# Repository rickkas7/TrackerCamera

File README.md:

# Tracker One Camera

This tutorial shows how to add a [4D Systems uCam-III](https://4dsystems.com.au/ucam-iii) to a Particle Tracker One to take pictures and upload them.

The caveat to this is that there is no built-in service for capturing or storing these image files in the cloud yet, but there's a simple demonstration server written in node.js that saves the files to disk. You can securely run this server even on a network using NAT (network address translation) without firewall changes. But the server is not intended to be used in production deployments. It's just an illustration of what is possible.

## The Process

While the camera may seem expensive, the reason for this specific camera is that it does JPEG compression in hardware. There is a serial interface to the MCU and a protocol for downloading the compressed image file. This eliminates the need to buffer the image in RAM to compress it. Since Particle devices generally have less than 80 Kbytes of free RAM, it's not possible to do compression of raw images on the MCU.

The camera connects to a small interface board which connects to the M8 connector on the Tracker One.

The image files are downloaded to the flash file system (LittleFS) on the Tracker for uploading when possible. This allows many images to be buffered even when there is currently no cellular signal.

When the Particle cloud is reachable, the image file is uploaded. The binary JPEG file is broken up into 423 byte chunks. Each of the chunks is Base64 encoded and published using the `NO_ACK` mode for speed and to minimize the data used by the ACKs. After the transmission is completed, the server sends either a done message, or a request to retransmit missing chunks. This repeats until all of the chunks have been received.

The image is verified using a SHA1 hash to make sure it was successfully received, and if so a message is sent from the server to tell the Tracker to delete the image. 

If you reboot the Tracker, it will upload any unsent files.

It takes about 25 seconds to upload a 320x240 pixel image. The image is only about 10 Kbytes, but the data usage is more than that because of the Base64 encoding needed to transport it in an event, and overhead.

It takes about 50 seconds to upload a 640x480 pixel image. 

## Connecting

The M8 (8mm) 8-pin connector on the Tracker One is standard, however it's not common. Some other connectors like M12 are more common, however, the 12mm connector would have required a taller enclosure to fit the larger connector. To simplify designs, Particle will provide a M8 female-to-wires cable, similar to this. This is for illustration only and the design may vary in the future.

The common use case will be to include a cable gland in your expansion enclosure, pass the wires through the gland, and terminate them on your custom expansion board.

You'd typically connect those wires to your custom expansion board using one of several methods:

- Terminate with pins in a PHR-8 to mate with a B8B-PH on your expansion board
- Terminate with screw terminals on your board
- Terminate by soldering the wires to your board

This example design is intended to be a prototype for illustration purposes only. It includes the same B8B-PH connector that is inside the Tracker One on the Tracker Carrier board. This connector is inexpensive and can be attached to the Tracker One Carrier Board or an eval adapter using an easy-to-build PHR-8 to PHR-8 cable:

If you are interested in prototyping designs intended to connect to the Tracker One M8 connector, but want to do it using the Tracker SoM Evaluation Board, you may be interested in [this project](https://github.com/rickkas7/M8-Eval-Adapter). It's only a set of design files, BoM, etc. and you'd need to fabricate the board and build it yourself; it's not available as a finished product. It also explains a bit more about how the M8 connector can be used.

## Hardware

There is a small board use to connect the Tracker One M8 connector to the camera. The board includes:

- Connector for connect to the M8 connector using screw terminals, a PHR-8 cable, or soldered wires.
- A XCL224 3.3V regulator
- Level shifters to convert the 5V camera UART signals to 3.3V needed by the Tracker One.
- A 5-pin camera connector

### Schematic

### Board Layout

### BoM

| Quantity | Part | Description | Example | Cost |
| :---: | :--- | :--- | :--- | ---: |
| 1 | C3 | Capacitor Ceramic 4.7uF 6.3V 0603 | [Murata GRM188R60J475KE19J](https://www.digikey.com/product-detail/en/murata-electronics-north-america/GRM188R60J475KE19J/490-6407-1-ND/3845604) | |
| 1 | C4 | Capacitor Ceramic 10uF 16V 0805 | [Murata GRM21BR61C106KE15L](https://www.digikey.com/product-detail/en/murata-electronics-north-america/GRM21BR61C106KE15L/490-3886-1-ND/965928) | |
| 1 | U2 | XCL224 3.3V regulator | [Torex XCL224A333D2-G](https://www.digikey.com/product-detail/en/torex-semiconductor-ltd/XCL224A333D2-G/893-1419-1-ND/8256121) |$ 2.43| 
| 2 | U1, U3 | IC TRNSLTR BIDIRECTIONAL SC70-6 | [TI SN74LVC1T45QDCKRQ1](https://www.digikey.com/product-detail/en/texas-instruments/SN74LVC1T45QDCKRQ1/296-39212-1-ND/5143211) | $0.60 |
|   | JP1 | Male Header Pins (8x0.1") | [Sullins PRPC040SAAN-RC](https://www.digikey.com/product-detail/en/PRPC040SAAN-RC/S1011EC-40-ND/2775214) | |

Choose one of:

| Quantity | Part | Description | Example | Cost | 
| :---: | :--- | :--- | :--- | ---: | 
| 1 | J1 | Conn SMD 8 position 2.00mm | [JST B8B-PH-SM4-TB(LF)(SN)](https://www.digikey.com/product-detail/en/jst-sales-america-inc/B8B-PH-SM4-TB-LF-SN/455-1740-1-ND/926837) | $1.00 |
|   | J2 | Male Header Pins (8x0.1") | [Sullins PRPC040SAAN-RC](https://www.digikey.com/product-detail/en/PRPC040SAAN-RC/S1011EC-40-ND/2775214) | |
| 1 | J2 | Screw Terminal Block 8x0.1" PTH | [On Shore OSTVN08A150](https://www.digikey.com/product-detail/en/on-shore-technology-inc/OSTVN08A150/ED10566-ND/1588868) | $2.36 | 

## Firmware

### Getting the Tracker Edge Firmware

The Tracker Edge firmware can be downloaded from Github:

[https://github.com/particle-iot/tracker-edge](https://github.com/particle-iot/tracker-edge)

After downloading the source, you will need to fetch the library dependencies. This can be done from a command prompt or terminal window with the git command line tools installed:

```
cd tracker-edge
git submodule init
git submodule update --recursive
```

Be sure to target 1.5.4-rc.1 or later for your build. Device OS 1.5.3 or later is required, only version 1.5.4-rc.1 and later are available in the full set of tools including Workbench, CLI, and Web IDE.

### Add the libraries

From the command palette in Workbench, **Particle: Install Library** then enter **CameraHelperRK**. 

If you prefer to edit project.properties directly, add these:

```
dependencies.CameraHelperRK=0.0.1
```

This library includes two other libraries, **uCamIII** to handle interacting with the camera and **Base64RK** to do the Base64 encoding.

### The full source

The firmware is pretty self-explanatory. There is a copy in source/main.cpp as well.

```cpp
#include "Particle.h"

#include "tracker_config.h"
#include "tracker.h"

#include "CameraHelperRK.h"

SYSTEM_THREAD(ENABLED);
SYSTEM_MODE(SEMI_AUTOMATIC);

PRODUCT_ID(TRACKER_PRODUCT_ID);
PRODUCT_VERSION(TRACKER_PRODUCT_VERSION);

SerialLogHandler logHandler(115200, LOG_LEVEL_INFO, {
    { "app.gps.nmea", LOG_LEVEL_INFO },
    { "app.gps.ubx",  LOG_LEVEL_INFO },
    { "ncp.at", LOG_LEVEL_INFO },
    { "net.ppp.client", LOG_LEVEL_INFO },
    { "app.cam", LOG_LEVEL_TRACE },
});

int takePictureHandler(String cmd);

CameraHelperTracker cameraHelper(Serial1, 115200);

void setup()
{
    Tracker::instance().init();

    Particle.function("takePicture", takePictureHandler);

    // Enable cloud configuration of settings    
    // cameraHelper.setupCloudConfig();

    // Start the camera interface
    // The CameraHelperTracker turns on the CAN_PWR to power the camera.
    cameraHelper.setup();

    Particle.connect();
}

void loop()
{
    Tracker::instance().loop();

    cameraHelper.loop();
}

int takePictureHandler(String cmd) 
{
    // Take a picture
    cameraHelper.takePicture();

    // Send the current location
    TrackerLocation::instance().triggerLocPub();
    return 0;
}

```

It registers a function so you can easy trigger taking a picture from the console.

```cpp
Particle.function("takePicture", takePictureHandler);
```

Of course you can easily do it from code as well:

```cpp
// Take a picture
cameraHelper.takePicture();
```

## Server

The server code is in the server directory. 

- Install the node dependencies:

```bash
npm install
```

- Get an [access token](https://docs.particle.io/reference/developer-tools/cli/#particle-token-create)

- Set it as an environment variable:

```bash
export AUTH_TOKEN=xxxxxxx
```

- Run the server. Be sure to specify the productId of your Tracker product!

```bash
node app.js --productId 1234
```

The server creates a directory `data`. Within that directory will be a directory each device ID that is publishing to the product.

When a picture is uploaded, the JPEG file is reconstituted and verified, and if the SHA1 hash matches, it's saved in the device directory with a timestamp as a filename. The most recent `loc` event for the same device is also saved as a .json file so you can get the matching location information.

### Cloud Configuration

If you uncomment the `setupCloudConfig()` call in main.cpp, you can configure the image parameters from the cloud!

```cpp
// Enable cloud configuration of settings    
// cameraHelper.setupCloudConfig();
```

The cloud configuration cannot be set from the console, but you can set it from the CLI using curl. 

```bash
curl -X PUT https://api.particle.io/v1/products/:productId/config/:deviceId?access_token=:accessToken -H "Content-Type: application/json" -d "{\"ucam\":{\"resolution\":5,\"contrast\":2,\"brightness\":2,\"exposure\":2}}"
```

Be sure to update:

`:productId` with your product ID
`:deviceId` with your Device ID that is set as a development device. If you want to change the contrast across your whole product leave off the slash and device ID.
`:accessToken` with a product access token. An easy way to get a temporary 

One easy way to get a temporary access token is to:

- Open the [console](https://console.particle.io).
- Open your Tracker product.
- Click on **Devices**.
- Open your device.
- In the **Events** tab, click on **View events from a terminal** (it's a button).
- Copy and paste the access token from the end of the command that is displayed.
- This token is invalidated when your close the console.

The parameters are:

- resolution:

  One of:
  - 1 80x60
  - 2 160x120
  - 3 160x128
  - 5 320x240 (default)
  - 7 640x480
  - 8 128x96
  - 9 128x128

- contrast:

  One of: 
  - 0 minimum
  - 1 low
  - 2 default
  - 3 high
  - 4 max

- brightness:

  One of: 
  - 0 minimum
  - 1 low
  - 2 default
  - 3 high
  - 4 max

- exposure:

  One of:
  - 0 exposure -2
  - 1 exposure -1
  - 2 exposure 0 (default)
  - 3 exposure +1
  - 4 exposure +2

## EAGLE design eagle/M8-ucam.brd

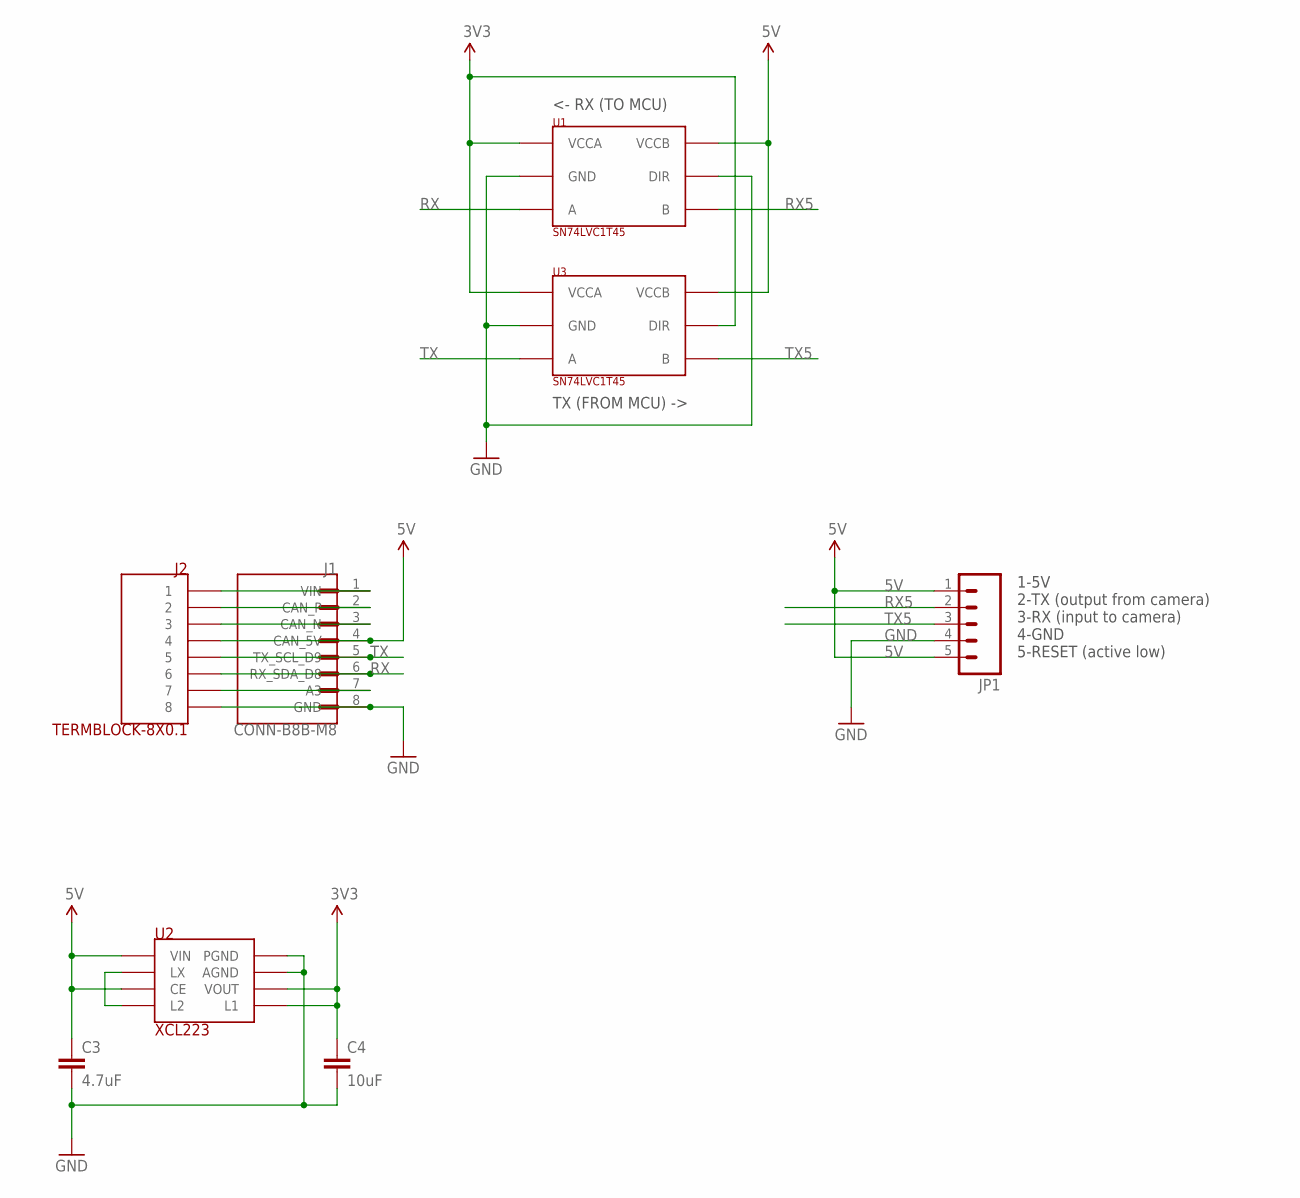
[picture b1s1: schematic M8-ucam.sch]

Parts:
C3: 4.7uF; 0603-CAP
C4: 10uF; 0603-CAP
J1: CONN-B8B-M8; JST_B8B-PH-SM4-TB(LF)(SN)
J2: TERMBLOCK-8X0.1
JP1: M05PTH; 1X05
U1, U3: SN74LVC1T45; SC70-TI
U2: XCL223; REG-XCL223-LESS-CREAM

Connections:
3V3: C4.1, U1.1 (VCCA), U2.3 (VOUT), U2.7 (L1), U3.1 (VCCA), U3.5 (DIR)
5V: C3.1, J1.4 (CAN_5V), J2.P$4 (4), JP1.1, JP1.5, U1.6 (VCCB), U2.4 (CE), U2.6 (VIN), U3.6 (VCCB)
A3: J1.7 (A3), J2.P$7 (7)
CAN_N: J1.3 (CAN_N), J2.P$3 (3)
CAN_P: J1.2 (CAN_P), J2.P$2 (2)
GND: C3.2, C4.2, J1.8 (GND), J2.P$8 (8), JP1.4, U1.2 (GND), U1.5 (DIR), U2.1 (PGND), U2.2 (AGND), U3.2 (GND)
LX: U2.5 (LX), U2.8 (L2)
RX: J1.6 (RX_SDA_D8), J2.P$6 (6), U1.3 (A)
RX5: JP1.2, U1.4 (B)
TX: J1.5 (TX_SCL_D9), J2.P$5 (5), U3.3 (A)
TX5: JP1.3, U3.4 (B)
VIN: J1.1 (VIN), J2.P$1 (1)

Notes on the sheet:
1-5V 2-TX (output from camera) 3-RX (input to camera) 4-GND 5-RESET (active low)
<- RX (TO MCU)
TX (FROM MCU) ->

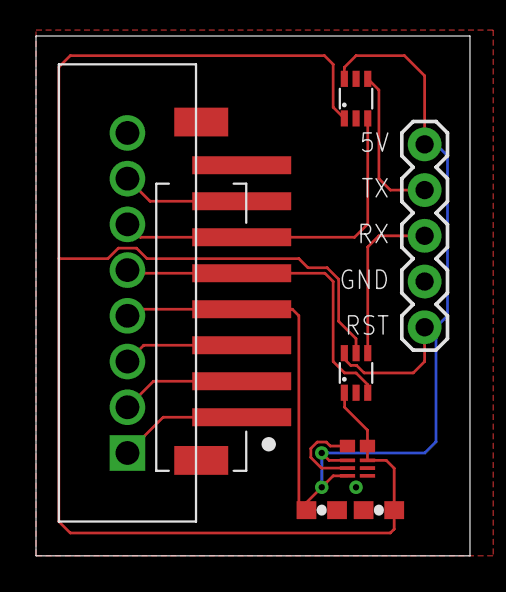
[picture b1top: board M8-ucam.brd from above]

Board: 2 copper layers, 24.1 x 28.9 mm, 8 parts (0 on the bottom side), 12 nets.

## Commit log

2020-07-26 Initial version
2020-07-26 Add Tracker Edge download instructions
2021-04-01 Bump y18n from 4.0.0 to 4.0.1 in /server
    Bumps [y18n](https://github.com/yargs/y18n) from 4.0.0 to 4.0.1.
    - [Release notes](https://github.com/yargs/y18n/releases)
    - [Changelog](https://github.com/yargs/y18n/blob/master/CHANGELOG.md)
    - [Commits](https://github.com/yargs/y18n/commits)
2022-12-06 Bump qs from 6.9.4 to 6.11.0 in /server
    Bumps [qs](https://github.com/ljharb/qs) from 6.9.4 to 6.11.0.
    - [Release notes](https://github.com/ljharb/qs/releases)
    - [Changelog](https://github.com/ljharb/qs/blob/main/CHANGELOG.md)
    - [Commits](https://github.com/ljharb/qs/compare/v6.9.4...v6.11.0)
    ---
    updated-dependencies:
2023-01-24 Bump cookiejar from 2.1.2 to 2.1.4 in /server
    Bumps [cookiejar](https://github.com/bmeck/node-cookiejar) from 2.1.2 to 2.1.4.
    - [Release notes](https://github.com/bmeck/node-cookiejar/releases)
    - [Commits](https://github.com/bmeck/node-cookiejar/commits)
    ---
    updated-dependencies:
    - dependency-name: cookiejar
2025-07-22 Fix dependencies
